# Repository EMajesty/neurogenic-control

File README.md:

# NEUROGENIC reference controller

Manufactured hardware authority and RP2040 firmware for the NEUROGENIC reference
surface. Start with the [hardware revision](docs/HARDWARE_REVISION.md),
[manifest](docs/HARDWARE_MANIFEST.md), [scanner](docs/INPUT_SCANNING.md),
[harness](docs/HARNESS_CONFIGURATION.md), and [diagnostics](docs/DIAGNOSTICS.md).
Manufactured-board work starts with the [acceptance quick start](docs/HARDWARE_ACCEPTANCE.md);
its structured output is defined by the [report format](docs/DIAGNOSTIC_REPORT_FORMAT.md).

## Reproducible development and tests

```sh
nix develop
scripts/test.sh
cmake -S . -B build/asan -DNEUROGENIC_SANITIZERS=ON
cmake --build build/asan
ctest --test-dir build/asan --output-on-failure
```

The lock pins nixpkgs and Pico SDK 2.1.1 with TinyUSB. The optional heavy KiCad
shell is `nix develop .#hardware`.

## Pico build and flash

```sh
nix develop
cmake -S firmware -B build/pico -G Ninja -DPICO_BOARD=pico
cmake --build build/pico
arm-none-eabi-size build/pico/neurogenic_controller.elf
picotool info build/pico/neurogenic_controller.uf2
```

Outputs are `build/pico/neurogenic_controller.elf`, `.uf2`, `.bin`, `.hex`, and
`.elf.map`. Hold BOOTSEL while connecting the original Pico and copy the UF2 to
`RPI-RP2`. Build directories are ignored.

```sh
python3 tools/neurogenic_diag.py --device /dev/ttyACM0 --command version
python3 tools/neurogenic_diag.py info --device /dev/ttyACM0
python3 tools/neurogenic_diag.py bringup --report acceptance.json
```

Illumination is disabled at boot, the harness is an unapproved example, and physical validation has not occurred. HW-003 adds PIO/DMA SK6812 and shared-clock TLC5947 drivers behind an explicit diagnostic enable and the combined 900 mA model. See [illumination drivers](docs/ILLUMINATION_DRIVERS.md), [power budget](docs/ILLUMINATION_POWER_BUDGET.md), and [HW-003 validation](docs/HW_003_VALIDATION.md).

```sh
nix develop
cmake -S firmware -B build/pico -G Ninja
cmake --build build/pico
sha256sum build/pico/neurogenic_controller.uf2
```

HW-004 adds the bounded semantic renderer and generated uncalibrated defaults. See [rendering](docs/ILLUMINATION_RENDERING.md), [calibration](docs/ILLUMINATION_CALIBRATION.md), and [validation](docs/HW_004_VALIDATION.md). Protocol remains 1.3 and physical calibration is not claimed.

HW-005 adds diagnostic-v1 identity/fingerprints, guided board acceptance,
standalone harness profiles, bounded stress/timing diagnostics and versioned
JSON/Markdown reports. Physical acceptance remains NOT RUN. See
[HW-005 validation](docs/HW_005_VALIDATION.md) and the source-grounded
[HW-006 proposal](docs/HW_006_PROTOCOL_PROPOSAL.md).

HW-006A pins and audits the normative upstream 1.3 contract and adds portable
golden-vector conformance tests without enabling a production endpoint:

```sh
python3 tools/verify_upstream_contract.py
python3 tools/generate_protocol_fixture_header.py --check
cmake -S . -B build/host -G Ninja
cmake --build build/host
ctest --test-dir build/host --output-on-failure
```

The provisional extension, compatibility matrix, and implementation handoffs
are in [the extension specification](docs/PROTOCOL_EXTENSION_SPEC.md),
[compatibility matrix](docs/PROTOCOL_COMPATIBILITY_MATRIX.md),
[HW-006B handoff](docs/HW_006B_HOST_HANDOFF.md), and
[HW-006C handoff](docs/HW_006C_FIRMWARE_HANDOFF.md). Extension identifiers are
not authoritative until committed by the main NEUROGENIC repository.

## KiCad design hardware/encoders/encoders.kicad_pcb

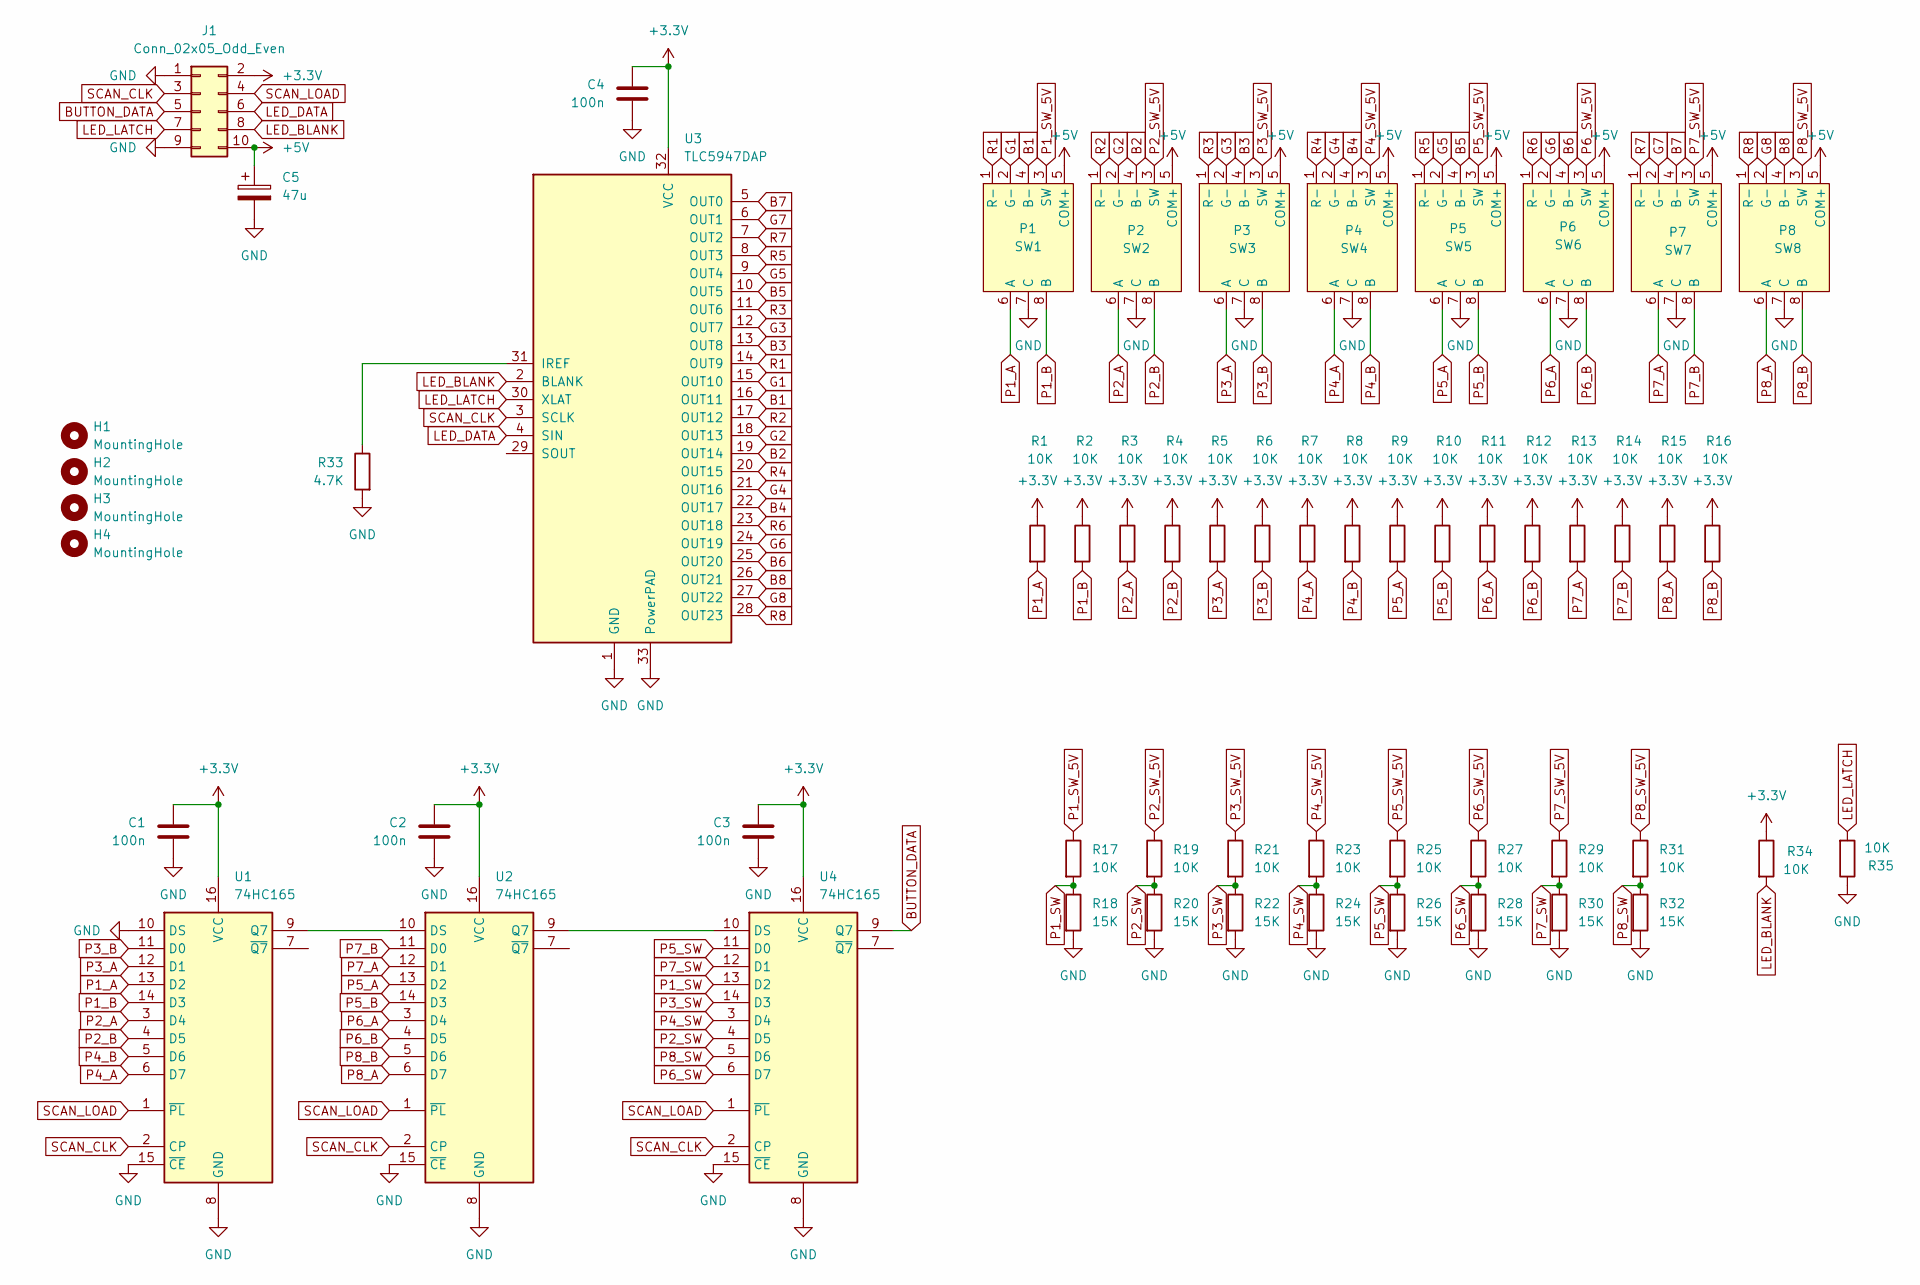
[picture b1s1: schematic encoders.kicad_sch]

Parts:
C1, C2, C3, C4: 100n; C_0805_2012Metric_Pad1.18x1.45mm_HandSolder
C5: 47u; CP_Radial_D6.3mm_P2.50mm
H1, H2, H3, H4: MountingHole; MountingHole_3.2mm_M3
J1: Conn_02x05_Odd_Even; IDC-Header_2x05_P2.54mm_Vertical
R1, R2, R3, R4, R5, R6, R7, R8, R9, R10, R11, R12, R13, R14, R15, R16, R17, R19, R21, R23, R25, R27, R29, R31, R34, R35: 10K; R_0805_2012Metric_Pad1.20x1.40mm_HandSolder
R18, R20, R22, R24, R26, R28, R30, R32: 15K; R_0805_2012Metric_Pad1.20x1.40mm_HandSolder
R33: 4.7K; R_0805_2012Metric_Pad1.20x1.40mm_HandSolder
SW1: P1; Bourns PEL12T
SW2: P2; Bourns PEL12T
SW3: P3; Bourns PEL12T
SW4: P4; Bourns PEL12T
SW5: P5; Bourns PEL12T
SW6: P6; Bourns PEL12T
SW7: P7; Bourns PEL12T
SW8: P8; Bourns PEL12T
U1, U2, U4: 74HC165; SOIC-16_3.9x9.9mm_P1.27mm
U3: TLC5947DAP; HTSSOP-32-1EP_6.1x11mm_P0.65mm_EP5.2x11mm_Mask4.11x4.36mm_T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

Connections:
+3.3V: C1.1, C2.1, C3.1, C4.1, J1.2, R1.1, R2.1, R3.1, R4.1, R5.1, R6.1, R7.1, R8.1, R9.1, R10.1, R11.1, R12.1, R13.1, R14.1, R15.1, R16.1, R34.1, U1.16 (VCC), U2.16 (VCC), U3.32 (VCC), U4.16 (VCC)
+5V: C5.1, J1.10, SW1.5 (COM+), SW2.5 (COM+), SW3.5 (COM+), SW4.5 (COM+), SW5.5 (COM+), SW6.5 (COM+), SW7.5 (COM+), SW8.5 (COM+)
B1: SW1.4 (B-), U3.16 (OUT11)
B2: SW2.4 (B-), U3.19 (OUT14)
B3: SW3.4 (B-), U3.13 (OUT8)
B4: SW4.4 (B-), U3.22 (OUT17)
B5: SW5.4 (B-), U3.10 (OUT5)
B6: SW6.4 (B-), U3.25 (OUT20)
B7: SW7.4 (B-), U3.5 (OUT0)
B8: SW8.4 (B-), U3.26 (OUT21)
BUTTON_DATA: J1.5, U4.9 (Q7)
G1: SW1.2 (G-), U3.15 (OUT10)
G2: SW2.2 (G-), U3.18 (OUT13)
G3: SW3.2 (G-), U3.12 (OUT7)
G4: SW4.2 (G-), U3.21 (OUT16)
G5: SW5.2 (G-), U3.9 (OUT4)
G6: SW6.2 (G-), U3.24 (OUT19)
G7: SW7.2 (G-), U3.6 (OUT1)
G8: SW8.2 (G-), U3.27 (OUT22)
GND: C1.2, C2.2, C3.2, C4.2, C5.2, J1.1, J1.9, R18.2, R20.2, R22.2, R24.2, R26.2, R28.2, R30.2, R32.2, R33.2, R35.1, SW1.7 (C), SW2.7 (C), SW3.7 (C), SW4.7 (C), SW5.7 (C), SW6.7 (C), SW7.7 (C), SW8.7 (C), U1.8 (GND), U1.10 (DS), U1.15 (~CE), U2.8 (GND), U2.15 (~CE), U3.1 (GND), U3.33 (PowerPAD), U4.8 (GND), U4.15 (~CE)
LED_BLANK: J1.8, R34.2, U3.2 (BLANK)
LED_DATA: J1.6, U3.4 (SIN)
LED_LATCH: J1.7, R35.2, U3.30 (XLAT)
unnamed: U1.9 (Q7), U2.10 (DS)
unnamed: U2.9 (Q7), U4.10 (DS)
unnamed: R33.1, U3.31 (IREF)
P1_A: R1.2, SW1.6 (A), U1.13 (D2)
P1_B: R2.2, SW1.8 (B), U1.14 (D3)
P1_SW: R17.2, R18.1, U4.13 (D2)
P1_SW_5V: R17.1, SW1.3 (SW)
P2_A: R3.2, SW2.6 (A), U1.3 (D4)
P2_B: R4.2, SW2.8 (B), U1.4 (D5)
P2_SW: R19.2, R20.1, U4.4 (D5)
P2_SW_5V: R19.1, SW2.3 (SW)
P3_A: R5.2, SW3.6 (A), U1.12 (D1)
P3_B: R6.2, SW3.8 (B), U1.11 (D0)
P3_SW: R21.2, R22.1, U4.14 (D3)
P3_SW_5V: R21.1, SW3.3 (SW)
P4_A: R7.2, SW4.6 (A), U1.6 (D7)
P4_B: R8.2, SW4.8 (B), U1.5 (D6)
P4_SW: R23.2, R24.1, U4.3 (D4)
P4_SW_5V: R23.1, SW4.3 (SW)
P5_A: R9.2, SW5.6 (A), U2.13 (D2)
P5_B: R10.2, SW5.8 (B), U2.14 (D3)
P5_SW: R25.2, R26.1, U4.11 (D0)
P5_SW_5V: R25.1, SW5.3 (SW)
P6_A: R11.2, SW6.6 (A), U2.3 (D4)
P6_B: R12.2, SW6.8 (B), U2.4 (D5)
P6_SW: R27.2, R28.1, U4.6 (D7)
P6_SW_5V: R27.1, SW6.3 (SW)
P7_A: R13.2, SW7.6 (A), U2.12 (D1)
P7_B: R14.2, SW7.8 (B), U2.11 (D0)
P7_SW: R29.2, R30.1, U4.12 (D1)
P7_SW_5V: R29.1, SW7.3 (SW)
P8_A: R15.2, SW8.6 (A), U2.6 (D7)
P8_B: R16.2, SW8.8 (B), U2.5 (D6)
P8_SW: R31.2, R32.1, U4.5 (D6)
P8_SW_5V: R31.1, SW8.3 (SW)
R1: SW1.1 (R-), U3.14 (OUT9)
R2: SW2.1 (R-), U3.17 (OUT12)
R3: SW3.1 (R-), U3.11 (OUT6)
R4: SW4.1 (R-), U3.20 (OUT15)
R5: SW5.1 (R-), U3.8 (OUT3)
R6: SW6.1 (R-), U3.23 (OUT18)
R7: SW7.1 (R-), U3.7 (OUT2)
R8: SW8.1 (R-), U3.28 (OUT23)
SCAN_CLK: J1.3, U1.2 (CP), U2.2 (CP), U3.3 (SCLK), U4.2 (CP)
SCAN_LOAD: J1.4, U1.1 (~PL), U2.1 (~PL), U4.1 (~PL)

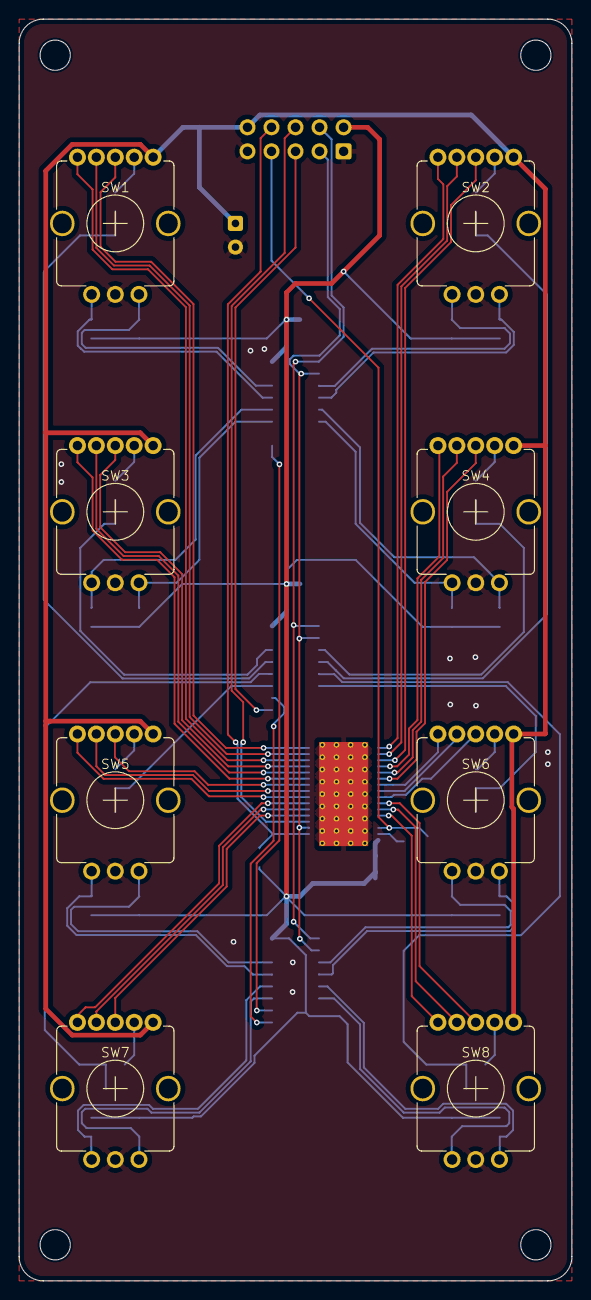
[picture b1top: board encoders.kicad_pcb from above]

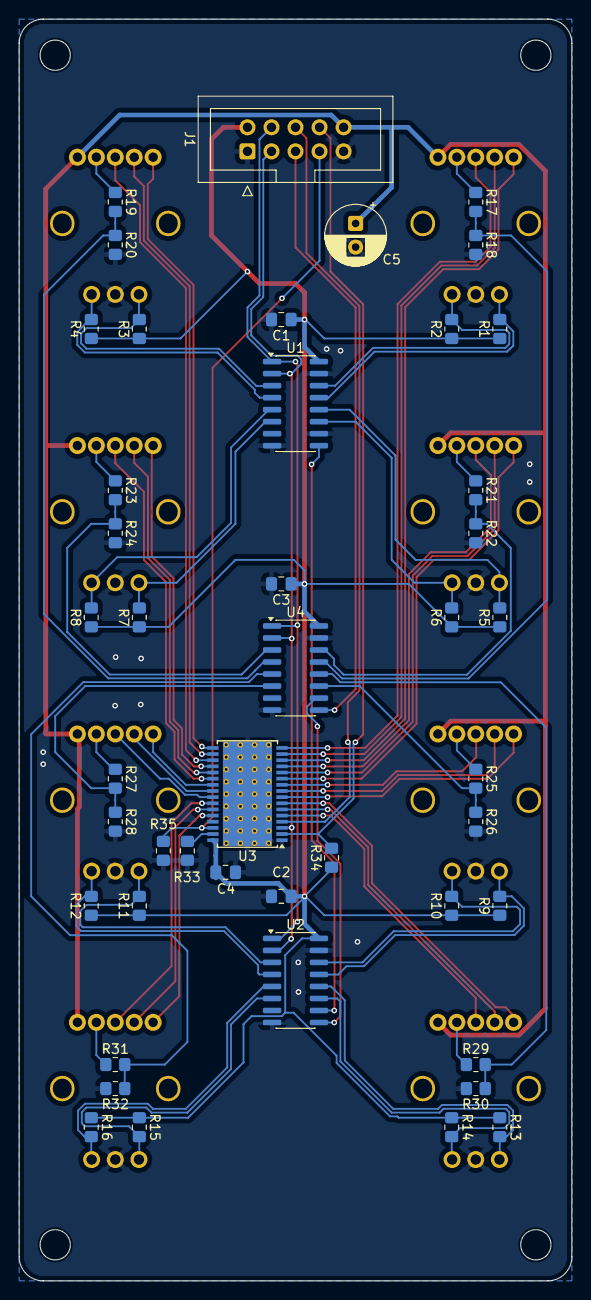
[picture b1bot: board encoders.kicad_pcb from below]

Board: 2 copper layers, 58.4 x 133.3 mm, 57 parts (45 on the bottom side), 68 nets.

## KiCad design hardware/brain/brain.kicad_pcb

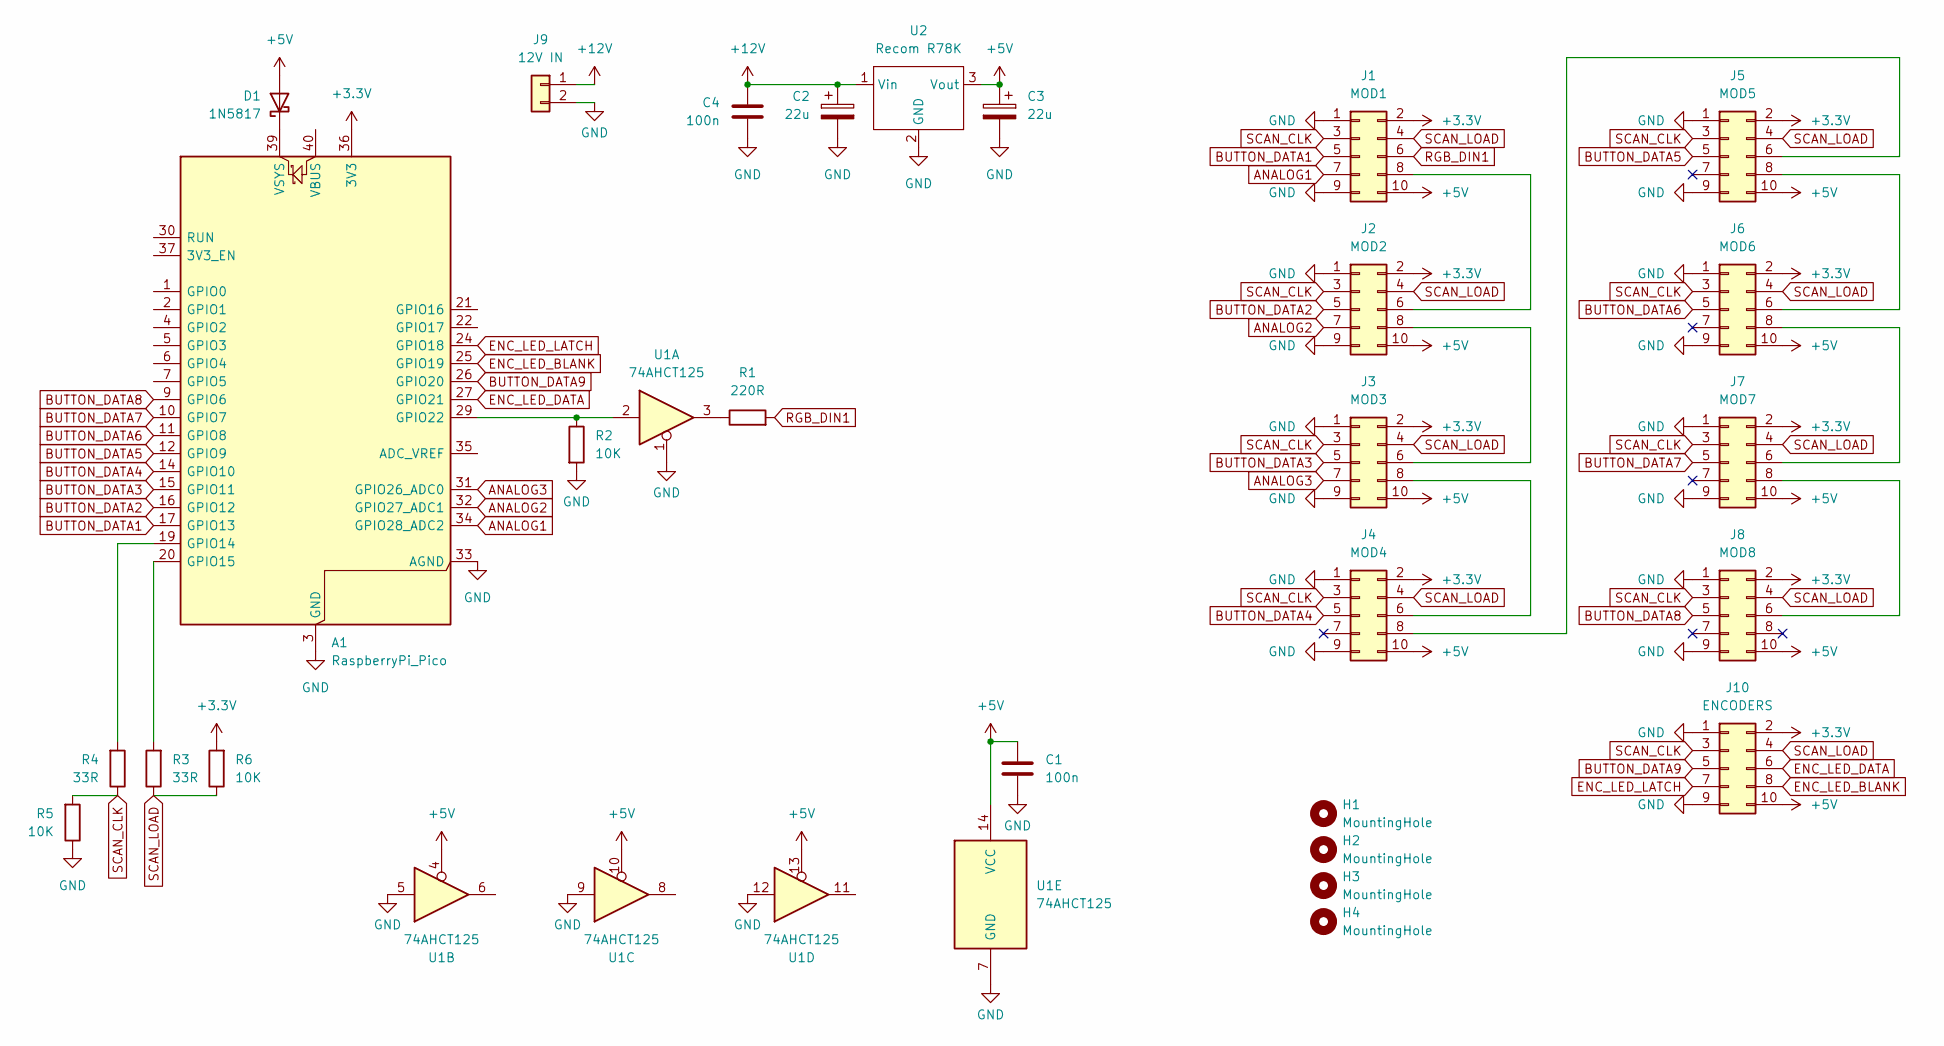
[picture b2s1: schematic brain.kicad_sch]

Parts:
A1: RaspberryPi_Pico; RaspberryPi_Pico_Common_Unspecified
C1, C4: 100n; C_0805_2012Metric_Pad1.18x1.45mm_HandSolder
C2, C3: 22u; CP_Radial_D5.0mm_P2.00mm
D1: 1N5817; D_DO-41_SOD81_P10.16mm_Horizontal
H1, H2, H3, H4: MountingHole; MountingHole_3.2mm_M3
J1: MOD1; IDC-Header_2x05_P2.54mm_Vertical
J2: MOD2; IDC-Header_2x05_P2.54mm_Vertical
J3: MOD3; IDC-Header_2x05_P2.54mm_Vertical
J4: MOD4; IDC-Header_2x05_P2.54mm_Vertical
J5: MOD5; IDC-Header_2x05_P2.54mm_Vertical
J6: MOD6; IDC-Header_2x05_P2.54mm_Vertical
J7: MOD7; IDC-Header_2x05_P2.54mm_Vertical
J8: MOD8; IDC-Header_2x05_P2.54mm_Vertical
J9: 12V IN; PinHeader_1x02_P2.54mm_Vertical
J10: ENCODERS; IDC-Header_2x05_P2.54mm_Vertical
R1: 220R; R_0805_2012Metric_Pad1.20x1.40mm_HandSolder
R2, R5, R6: 10K; R_0805_2012Metric_Pad1.20x1.40mm_HandSolder
R3, R4: 33R; R_0805_2012Metric_Pad1.20x1.40mm_HandSolder
U1: 74AHCT125; SOIC-14_3.9x8.7mm_P1.27mm
U2: Recom R78K

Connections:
+3.3V: A1.36 (3V3), J1.2, J2.2, J3.2, J4.2, J5.2, J6.2, J7.2, J8.2, J10.2, R6.2
+5V: C1.1, C3.1, D1.2 (A), J1.10, J2.10, J3.10, J4.10, J5.10, J6.10, J7.10, J8.10, J10.10, U1.4, U1.10, U1.13, U1.14 (VCC), U2.3 (Vout)
+12V: C2.1, C4.1, J9.1, U2.1 (Vin)
ANALOG1: A1.34 (GPIO28_ADC2), J1.7
ANALOG2: A1.32 (GPIO27_ADC1), J2.7
ANALOG3: A1.31 (GPIO26_ADC0), J3.7
BUTTON_DATA1: A1.17 (GPIO13), J1.5
BUTTON_DATA2: A1.16 (GPIO12), J2.5
BUTTON_DATA3: A1.15 (GPIO11), J3.5
BUTTON_DATA4: A1.14 (GPIO10), J4.5
BUTTON_DATA5: A1.12 (GPIO9), J5.5
BUTTON_DATA6: A1.11 (GPIO8), J6.5
BUTTON_DATA7: A1.10 (GPIO7), J7.5
BUTTON_DATA8: A1.9 (GPIO6), J8.5
BUTTON_DATA9: A1.26 (GPIO20), J10.5
ENC_LED_BLANK: A1.25 (GPIO19), J10.8
ENC_LED_DATA: A1.27 (GPIO21), J10.6
ENC_LED_LATCH: A1.24 (GPIO18), J10.7
GND: A1.3 (GND), A1.8 (GND), A1.13 (GND), A1.18 (GND), A1.23 (GND), A1.28 (GND), A1.33 (AGND), A1.38 (GND), C1.2, C2.2, C3.2, C4.2, J1.1, J1.9, J2.1, J2.9, J3.1, J3.9, J4.1, J4.9, J5.1, J5.9, J6.1, J6.9, J7.1, J7.9, J8.1, J8.9, J9.2, J10.1, J10.9, R2.2, R5.1, U1.1, U1.5, U1.7 (GND), U1.9, U1.12, U2.2 (GND)
unnamed: A1.19 (GPIO14), R4.2
unnamed: A1.20 (GPIO15), R3.2
unnamed: A1.29 (GPIO22), R2.1, U1.2
unnamed: A1.39 (VSYS), D1.1 (K)
unnamed: J1.8, J2.6
unnamed: J2.8, J3.6
unnamed: J3.8, J4.6
unnamed: J4.8, J5.6
unnamed: J5.8, J6.6
unnamed: J6.8, J7.6
unnamed: J7.8, J8.6
unnamed: R1.1, U1.3
RGB_DIN1: J1.6, R1.2
SCAN_CLK: J1.3, J2.3, J3.3, J4.3, J5.3, J6.3, J7.3, J8.3, J10.3, R4.1, R5.2
SCAN_LOAD: J1.4, J2.4, J3.4, J4.4, J5.4, J6.4, J7.4, J8.4, J10.4, R3.1, R6.1

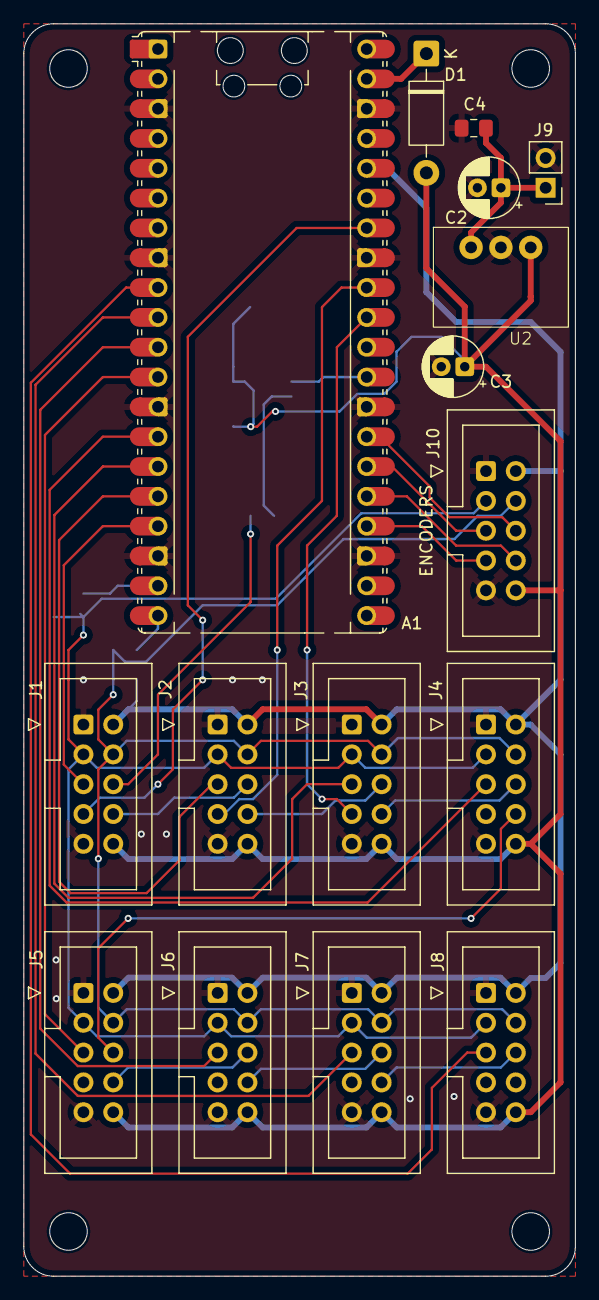
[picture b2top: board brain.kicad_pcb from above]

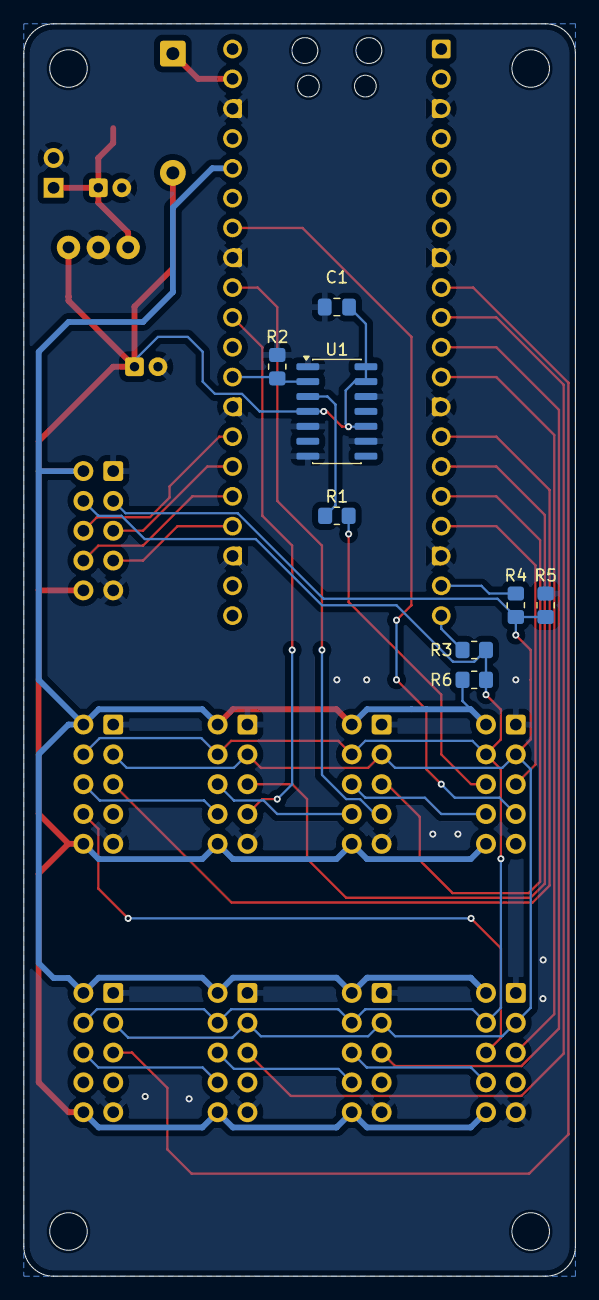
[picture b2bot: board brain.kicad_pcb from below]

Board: 2 copper layers, 47.0 x 106.7 mm, 28 parts (8 on the bottom side), 34 nets.

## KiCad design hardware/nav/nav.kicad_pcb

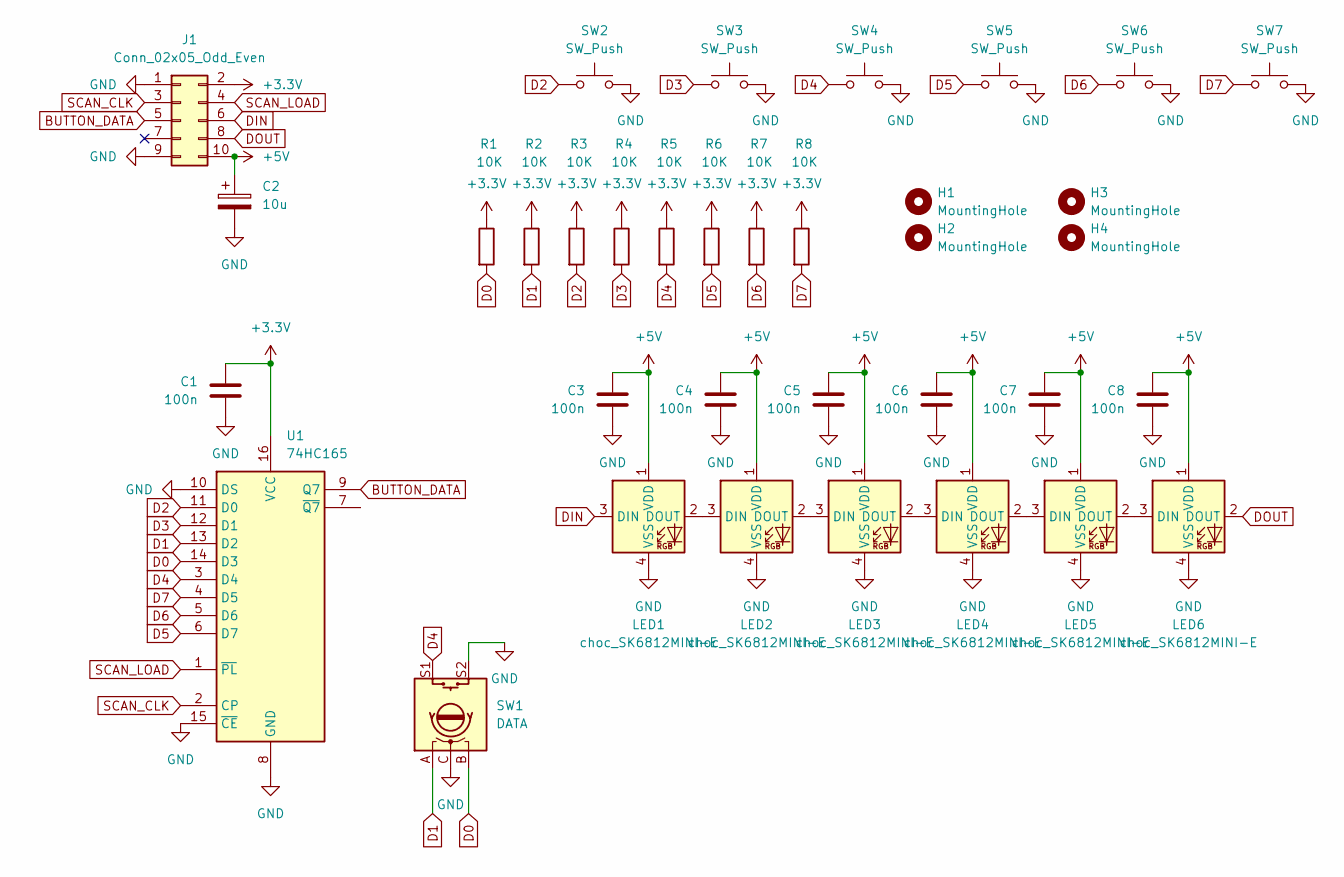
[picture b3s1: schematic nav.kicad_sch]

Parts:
C1, C3, C4, C5, C6, C7, C8: 100n; C_0805_2012Metric_Pad1.18x1.45mm_HandSolder
C2: 10u; CP_Radial_D4.0mm_P2.00mm
H1, H2, H3, H4: MountingHole; MountingHole_3.2mm_M3
J1: Conn_02x05_Odd_Even; IDC-Header_2x05_P2.54mm_Vertical
LED1, LED2, LED3, LED4, LED5, LED6: choc_SK6812MINI-E; LED_choc_6028R-ROT
R1, R2, R3, R4, R5, R6, R7, R8: 10K; R_0805_2012Metric_Pad1.20x1.40mm_HandSolder
SW1: DATA; Bourns PEC11H
SW2, SW3, SW4, SW5, SW6, SW7: SW_Push; SW_choc_v1_1u
U1: 74HC165; SOIC-16_3.9x9.9mm_P1.27mm

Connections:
+3.3V: C1.1, J1.2, R1.1, R2.1, R3.1, R4.1, R5.1, R6.1, R7.1, R8.1, U1.16 (VCC)
+5V: C2.1, C3.1, C4.1, C5.1, C6.1, C7.1, C8.1, J1.10, LED1.1 (VDD), LED2.1 (VDD), LED3.1 (VDD), LED4.1 (VDD), LED5.1 (VDD), LED6.1 (VDD)
BUTTON_DATA: J1.5, U1.9 (Q7)
D0: R1.2, SW1.B, U1.14 (D3)
D1: R2.2, SW1.A, U1.13 (D2)
D2: R3.2, SW2.1, U1.11 (D0)
D3: R4.2, SW3.1, U1.12 (D1)
D4: R5.2, SW1.S1, SW4.1, U1.3 (D4)
D5: R6.2, SW5.1, U1.6 (D7)
D6: R7.2, SW6.1, U1.5 (D6)
D7: R8.2, SW7.1, U1.4 (D5)
DIN: J1.6, LED1.3 (DIN)
DOUT: J1.8, LED6.2 (DOUT)
GND: C1.2, C2.2, C3.2, C4.2, C5.2, C6.2, C7.2, C8.2, J1.1, J1.9, LED1.4 (VSS), LED2.4 (VSS), LED3.4 (VSS), LED4.4 (VSS), LED5.4 (VSS), LED6.4 (VSS), SW1.C, SW1.S2, SW2.2, SW3.2, SW4.2, SW5.2, SW6.2, SW7.2, U1.8 (GND), U1.10 (DS), U1.15 (~CE)
unnamed: LED1.2 (DOUT), LED2.3 (DIN)
unnamed: LED2.2 (DOUT), LED3.3 (DIN)
unnamed: LED3.2 (DOUT), LED4.3 (DIN)
unnamed: LED4.2 (DOUT), LED5.3 (DIN)
unnamed: LED5.2 (DOUT), LED6.3 (DIN)
SCAN_CLK: J1.3, U1.2 (CP)
SCAN_LOAD: J1.4, U1.1 (~PL)

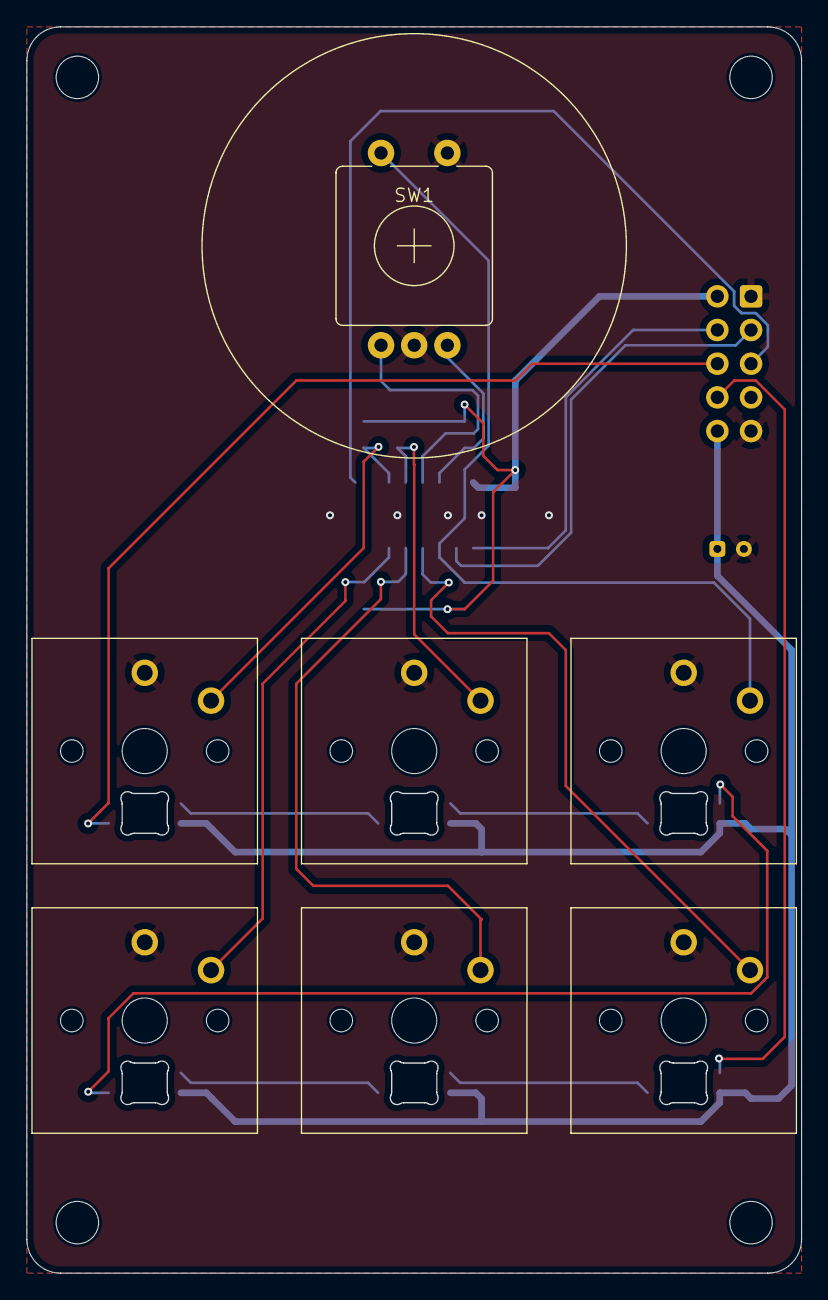
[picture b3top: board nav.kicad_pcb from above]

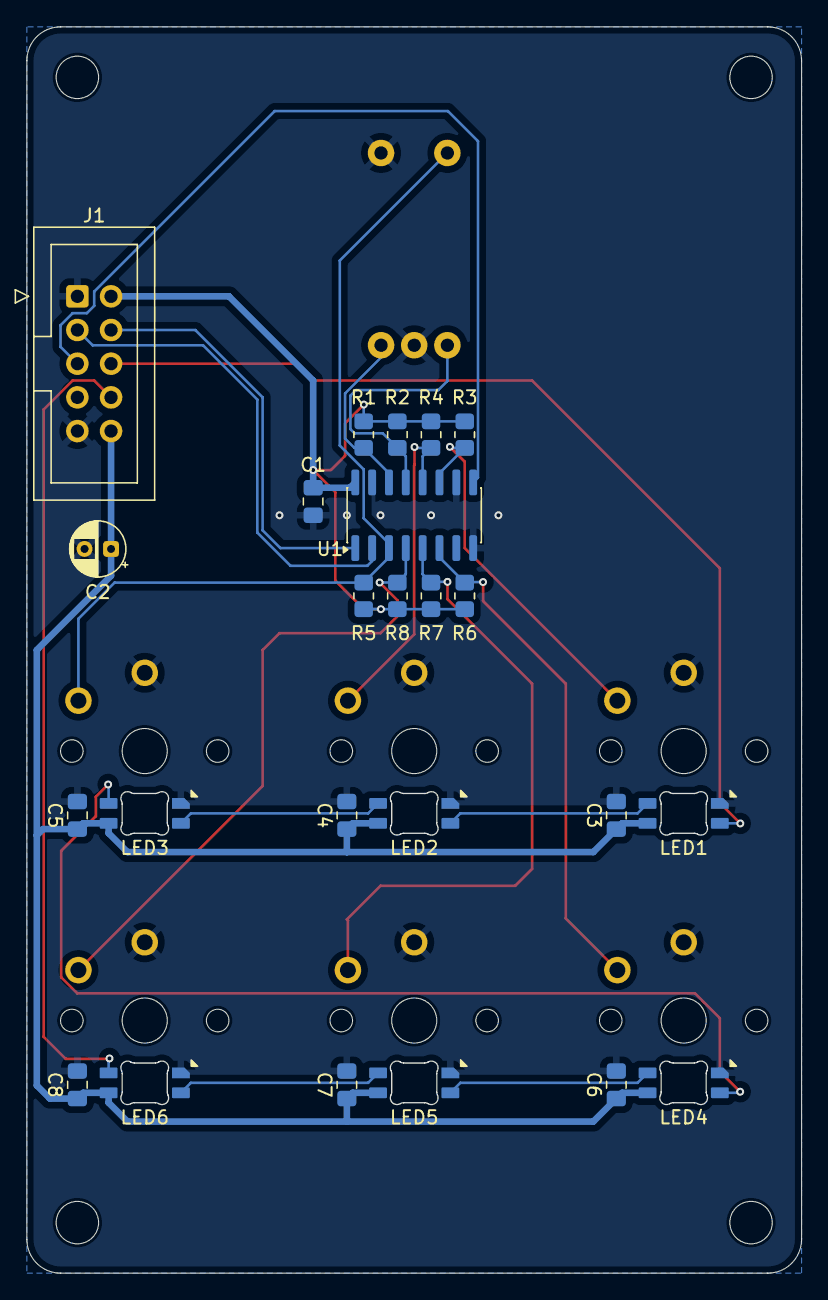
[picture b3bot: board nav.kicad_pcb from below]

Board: 2 copper layers, 58.4 x 94.0 mm, 35 parts (24 on the bottom side), 21 nets.

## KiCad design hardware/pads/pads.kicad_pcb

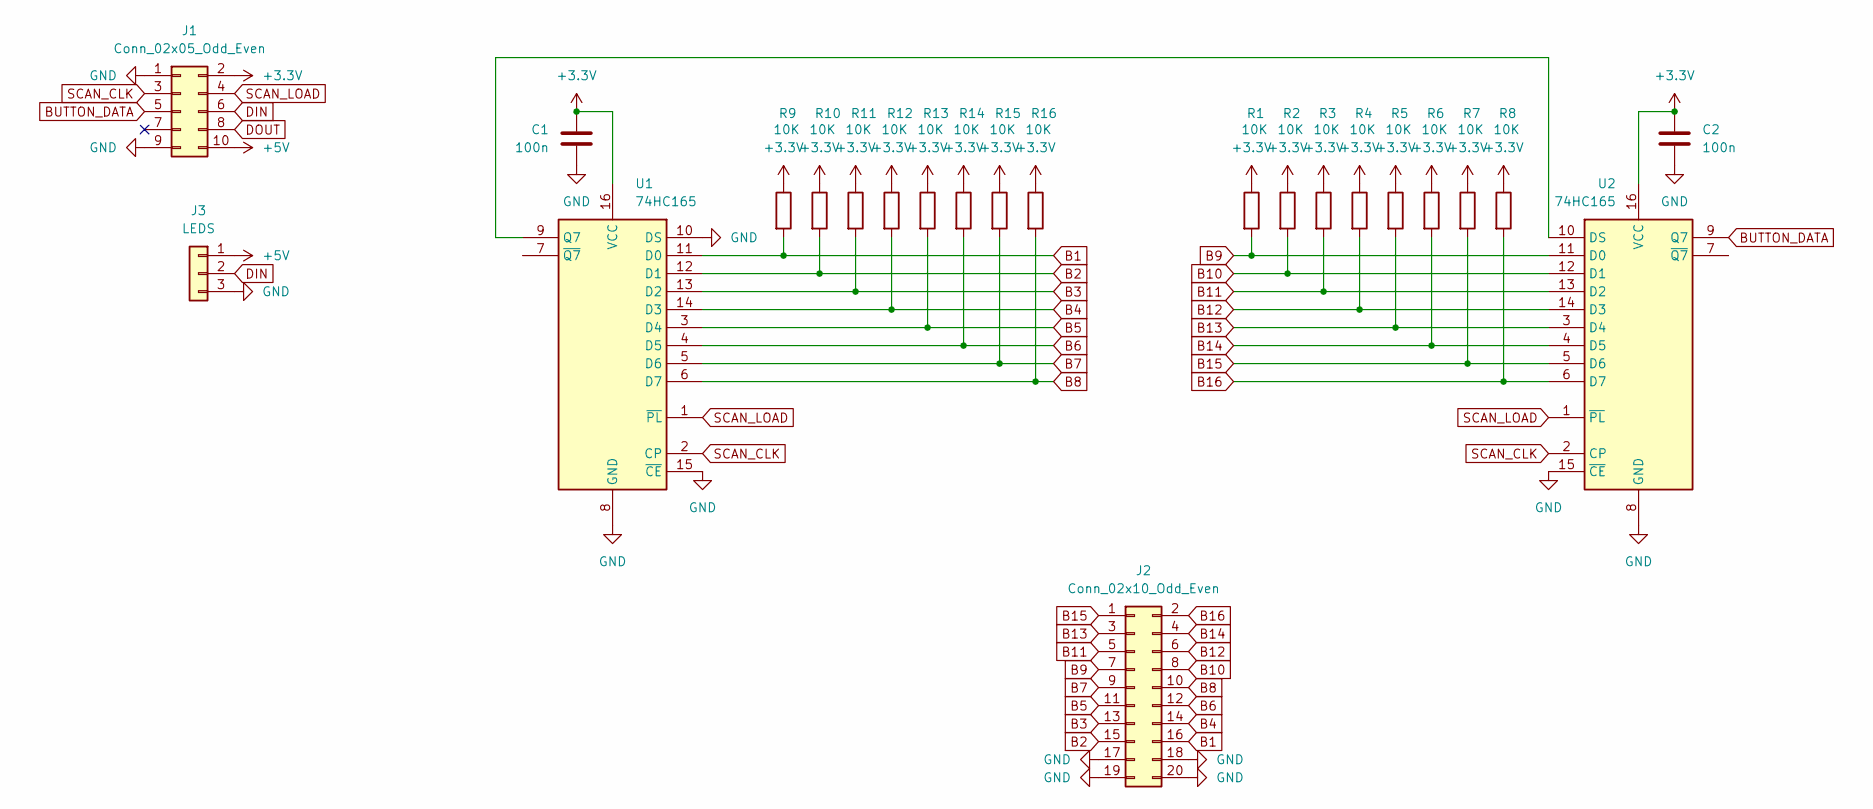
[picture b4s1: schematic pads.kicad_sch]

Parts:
C1, C2: 100n; C_0805_2012Metric_Pad1.18x1.45mm_HandSolder
J1: Conn_02x05_Odd_Even; IDC-Header_2x05_P2.54mm_Vertical
J2: Conn_02x10_Odd_Even; IDC-Header_2x10_P2.54mm_Vertical
J3: LEDS; PinHeader_1x03_P2.54mm_Vertical
R1, R2, R3, R4, R5, R6, R7, R8, R9, R10, R11, R12, R13, R14, R15, R16: 10K; R_0805_2012Metric_Pad1.20x1.40mm_HandSolder
U1, U2: 74HC165; SOIC-16_3.9x9.9mm_P1.27mm

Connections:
+3.3V: C1.1, C2.1, J1.2, R1.1, R2.1, R3.1, R4.1, R5.1, R6.1, R7.1, R8.1, R9.1, R10.1, R11.1, R12.1, R13.1, R14.1, R15.1, R16.1, U1.16 (VCC), U2.16 (VCC)
+5V: J1.10, J3.1
B1: J2.16, R9.2, U1.11 (D0)
B2: J2.15, R10.2, U1.12 (D1)
B3: J2.13, R11.2, U1.13 (D2)
B4: J2.14, R12.2, U1.14 (D3)
B5: J2.11, R13.2, U1.3 (D4)
B6: J2.12, R14.2, U1.4 (D5)
B7: J2.9, R15.2, U1.5 (D6)
B8: J2.10, R16.2, U1.6 (D7)
B9: J2.7, R1.2, U2.11 (D0)
B10: J2.8, R2.2, U2.12 (D1)
B11: J2.5, R3.2, U2.13 (D2)
B12: J2.6, R4.2, U2.14 (D3)
B13: J2.3, R5.2, U2.3 (D4)
B14: J2.4, R6.2, U2.4 (D5)
B15: J2.1, R7.2, U2.5 (D6)
B16: J2.2, R8.2, U2.6 (D7)
BUTTON_DATA: J1.5, U2.9 (Q7)
DIN: J1.6, J3.2
DOUT: J1.8
GND: C1.2, C2.2, J1.1, J1.9, J2.17, J2.18, J2.19, J2.20, J3.3, U1.8 (GND), U1.10 (DS), U1.15 (~CE), U2.8 (GND), U2.15 (~CE)
unnamed: U1.9 (Q7), U2.10 (DS)
SCAN_CLK: J1.3, U1.2 (CP), U2.2 (CP)
SCAN_LOAD: J1.4, U1.1 (~PL), U2.1 (~PL)

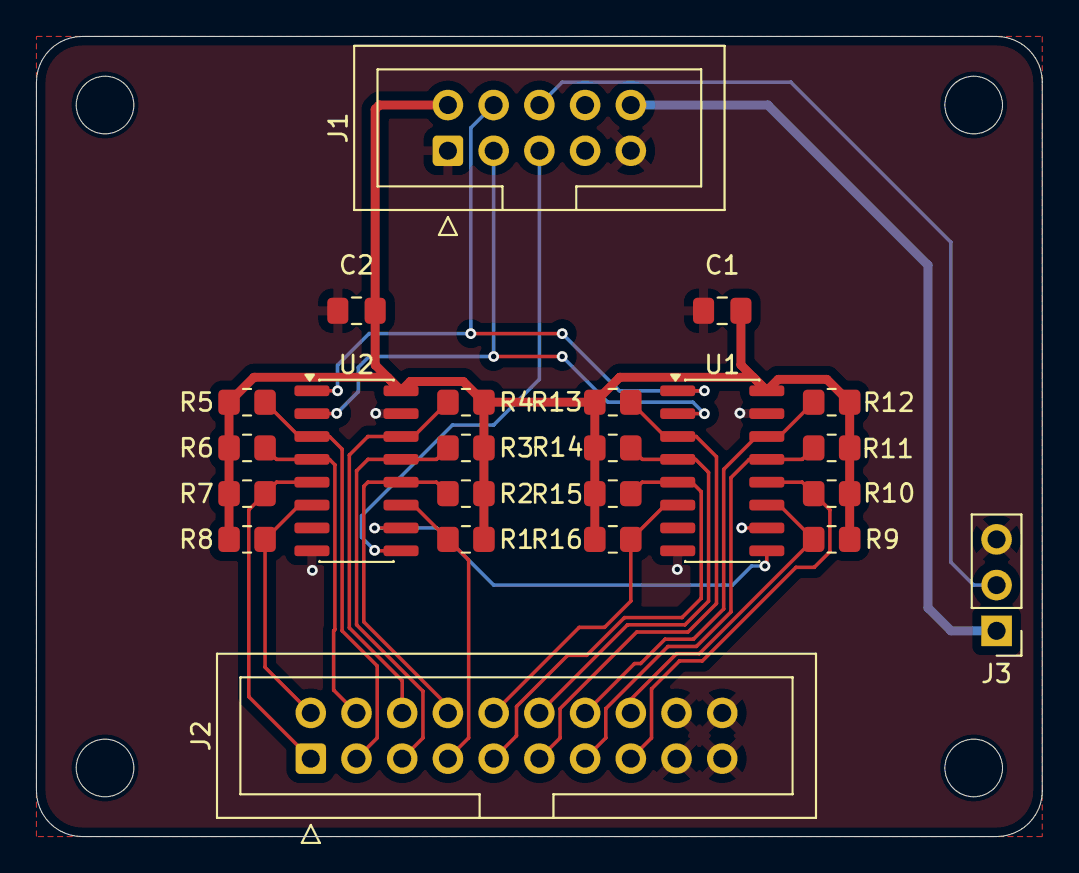
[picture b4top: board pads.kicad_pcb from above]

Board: 2 copper layers, 55.9 x 44.5 mm, 23 parts (0 on the bottom side), 24 nets.
